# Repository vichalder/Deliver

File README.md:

# Deliver phase
This is where all the files created for the project are stored.

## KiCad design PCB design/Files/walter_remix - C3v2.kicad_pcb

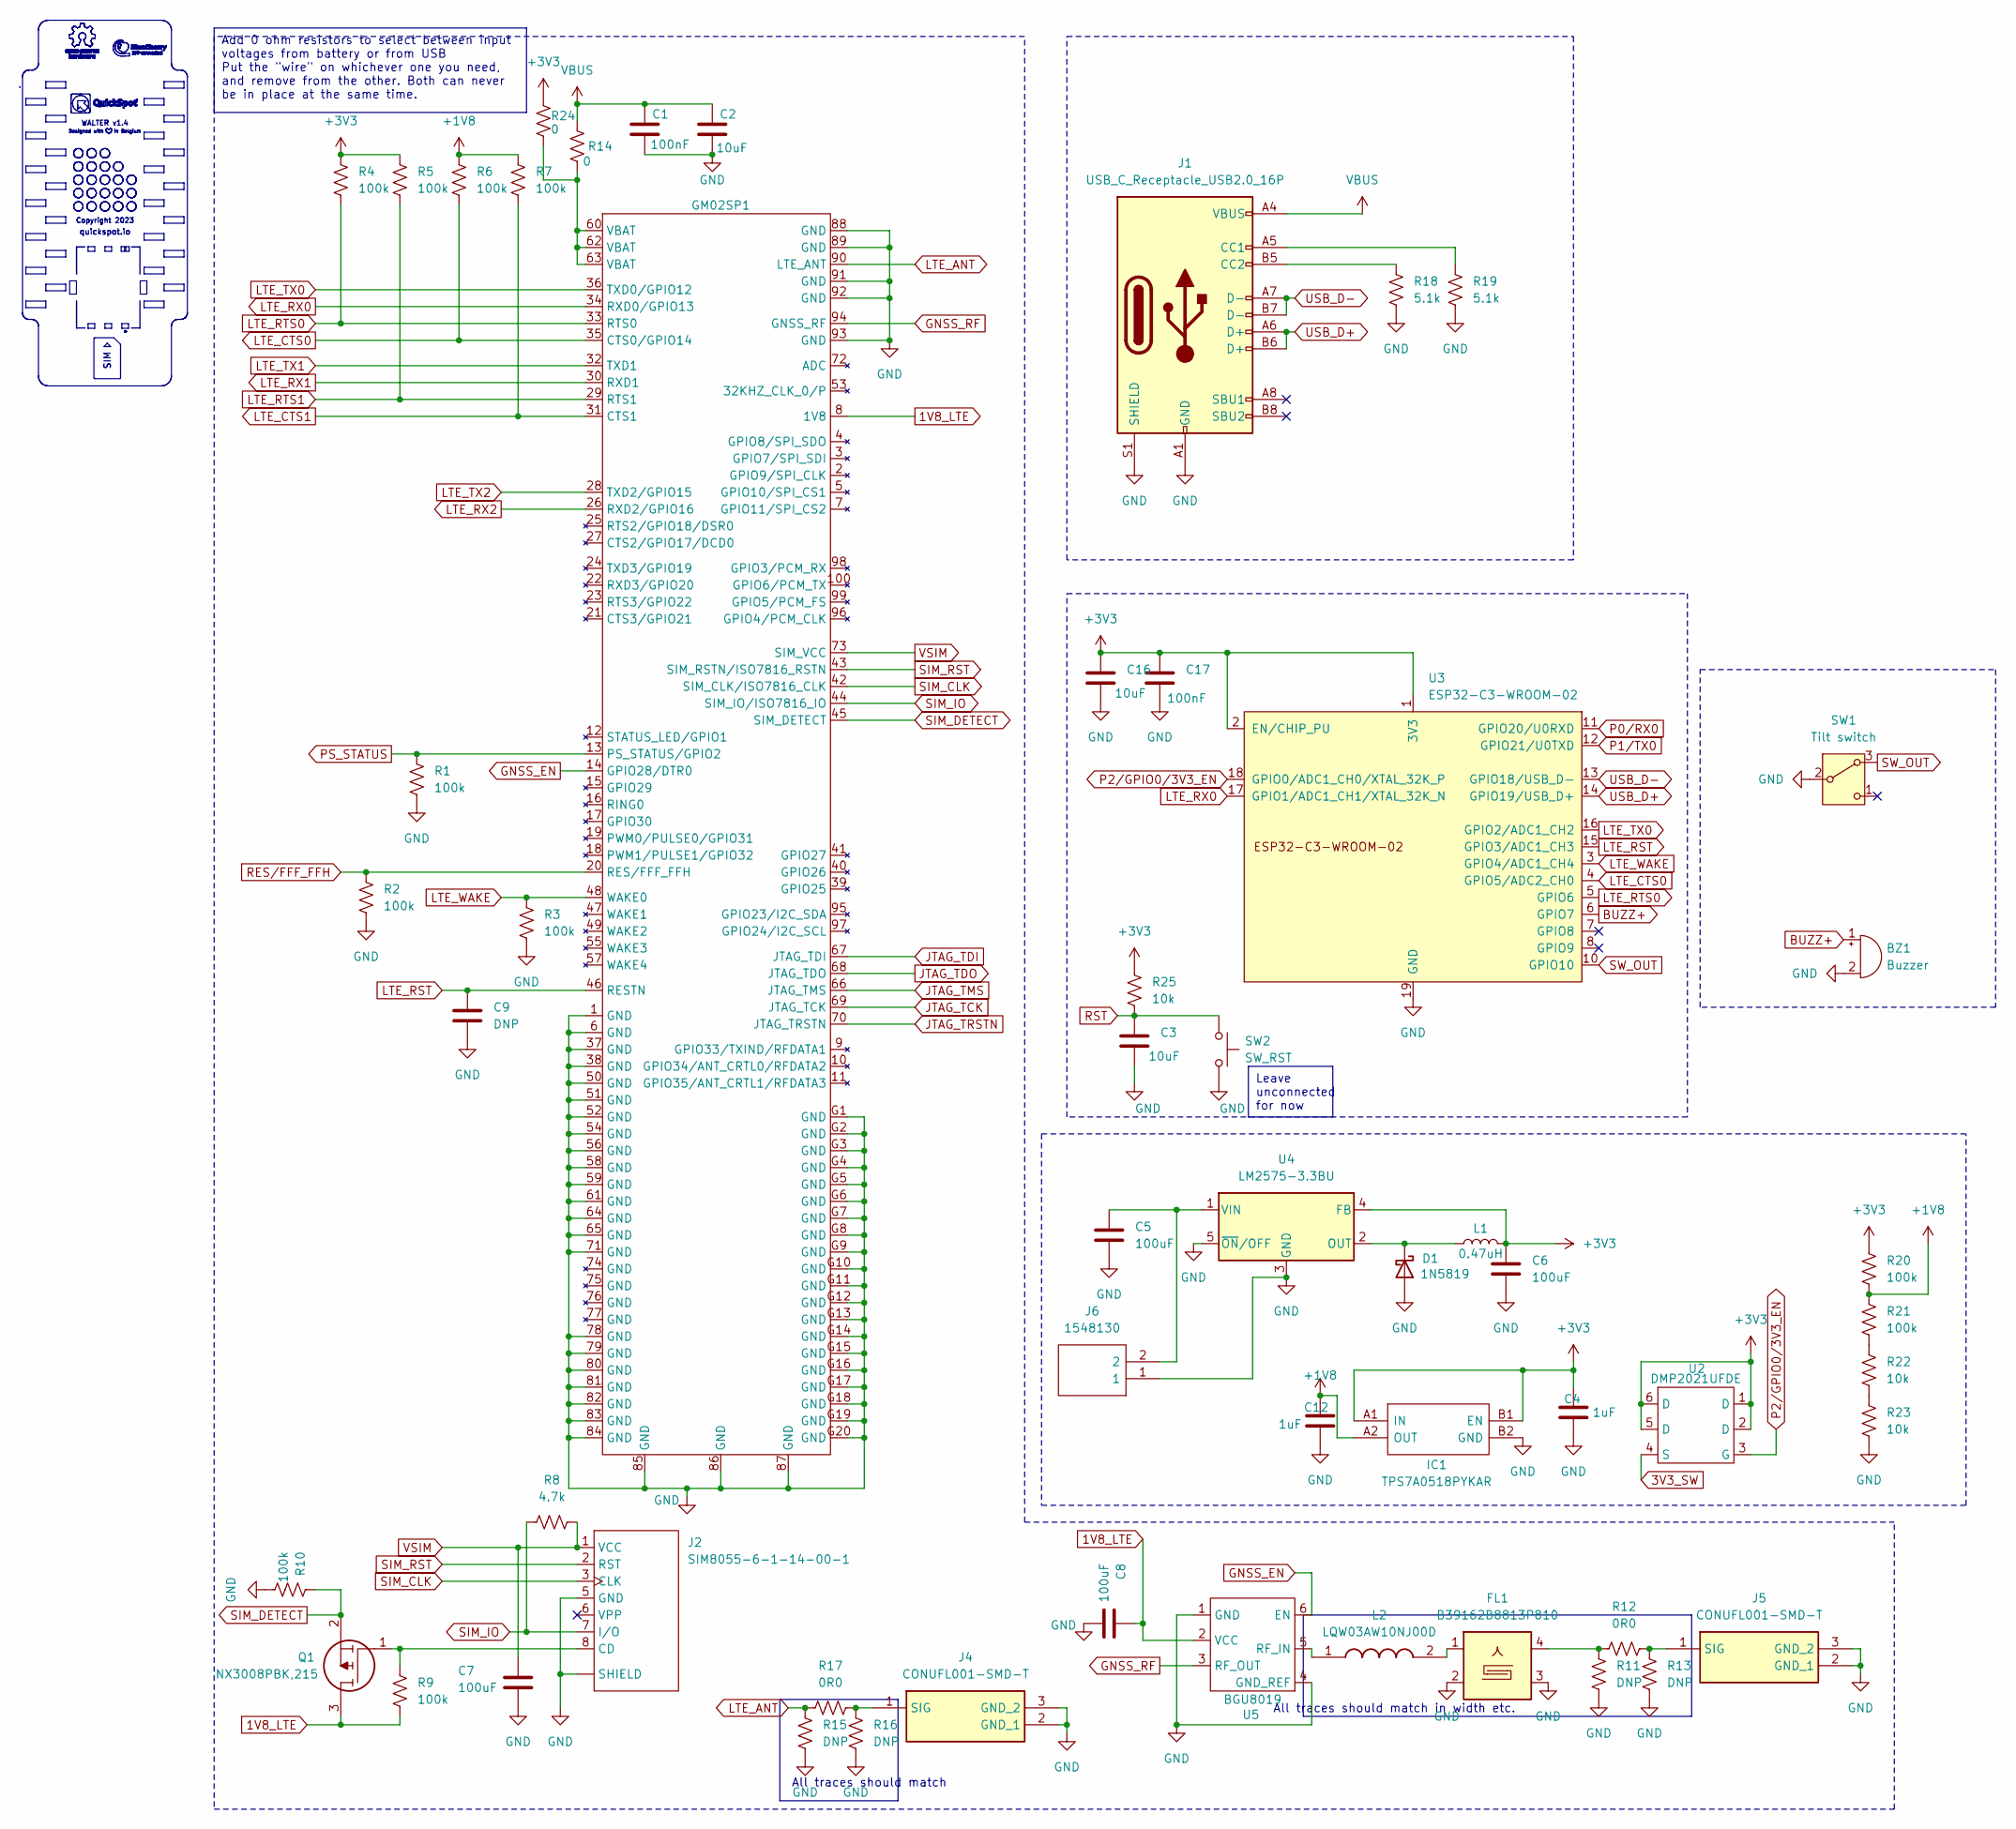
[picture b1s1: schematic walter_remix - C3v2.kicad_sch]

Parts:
BZ1: Buzzer; Buzzer_CUI_CPT-9019S-SMT
C1, C17: 100nF; C_0201_0603Metric
C2, C3, C16: 10uF; C_0201_0603Metric
C4, C12: 1uF; C_0201_0603Metric
C5, C6, C7, C8: 100uF; C_0201_0603Metric
C9: DNP; C_0201_0603Metric
D1: 1N5819; SOD3715X145N
FL1: B39162B8813P810; Filter_1109-5_1.1x0.9mm
GM02SP1: Sequans Monarch 2 GM02SP
IC1: TPS7A0518PYKAR; BGA4C35P2X2_66X66X40; Mouser Part Number 595-TPS7A0518PYKAR
J1: USB_C_Receptacle_USB2.0_16P; USB_C_Receptacle_HCTL_HC-TYPE-C-16P-01A
J2: SIM8055-6-1-14-00-1; SIM8055-6-1-14-01-A
J4, J5: CONUFL001-SMD-T; Mouser Part Number N/A
J6: 1548130; Mouser Part Number 651-1548130
L1: 0.47uH; Inductor 0.47uH
L2: LQW03AW10NJ00D; Mouser Part Number 81-LQW03AW10NJ00D
Q1: NX3008PBK,215; NX3008PBK215; Mouser Part Number 771-NX3008PBK,215
R1, R2, R3, R4, R5, R6, R7, R9, R10, R20, R21: 100k; R_0201_0603Metric
R8: 4.7k; R_0201_0603Metric
R11, R13, R15, R16: DNP; R_0201_0603Metric
R12, R17: 0R0; R_0201_0603Metric
R14, R24: 0; R_0201_0603Metric
R18, R19: 5.1k; R_0201_0603Metric
R22, R23, R25: 10k; R_0201_0603Metric
SW1: Tilt switch; Adafruit_vibration_sensor_tall
SW2: SW_RST; PTS815SJK250SMTRLFS
U2: DMP2021UFDE
U3: ESP32-C3-WROOM-02
U4: LM2575-3.3BU; TO-263-5_TabPin3
U5: BGU8019

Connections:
1V8_LTE: C8.1, GM02SP1.8 (1V8), Q1.3, R9.1, U5.2 (VCC)
+1V8: C12.1, IC1.A2 (OUT), R6.1, R7.1, R20.2, R21.1
+3V3: C4.1, C6.1, C16.1, C17.1, IC1.A1 (IN), IC1.B1 (EN), L1.2, R4.1, R5.1, R20.1, R24.1, R25.1, U2.1 (D), U2.2 (D), U2.5 (D), U2.6 (D), U3.1 (3V3), U3.2 (EN/CHIP_PU), U4.4 (FB)
BUZZ+: BZ1.1 (+), U3.6 (GPIO7)
GND: BZ1.2 (-), C1.2, C2.2, C3.2, C4.2, C5.2, C6.2, C7.2, C8.2, C9.2, C12.2, C16.2, C17.2, D1.2 (A), D1.A, FL1.2, FL1.3, FL1.5, GM02SP1.1 (GND), GM02SP1.6 (GND), GM02SP1.37 (GND), GM02SP1.38 (GND), GM02SP1.50 (GND), GM02SP1.51 (GND), GM02SP1.52 (GND), GM02SP1.54 (GND), GM02SP1.56 (GND), GM02SP1.58 (GND), GM02SP1.59 (GND), GM02SP1.61 (GND), GM02SP1.64 (GND), GM02SP1.65 (GND), GM02SP1.71 (GND), GM02SP1.78 (GND), GM02SP1.79 (GND), GM02SP1.80 (GND), GM02SP1.81 (GND), GM02SP1.82 (GND), GM02SP1.83 (GND), GM02SP1.84 (GND), GM02SP1.85 (GND), GM02SP1.86 (GND), GM02SP1.87 (GND), GM02SP1.88 (GND), GM02SP1.89 (GND), GM02SP1.91 (GND), GM02SP1.92 (GND), GM02SP1.93 (GND), GM02SP1.G1 (GND), GM02SP1.G2 (GND), GM02SP1.G3 (GND), GM02SP1.G4 (GND), GM02SP1.G5 (GND), GM02SP1.G6 (GND), GM02SP1.G7 (GND), GM02SP1.G8 (GND), GM02SP1.G9 (GND), GM02SP1.G10 (GND), GM02SP1.G11 (GND), GM02SP1.G12 (GND), GM02SP1.G13 (GND), GM02SP1.G14 (GND), GM02SP1.G15 (GND), GM02SP1.G16 (GND), GM02SP1.G17 (GND), GM02SP1.G18 (GND), GM02SP1.G19 (GND), GM02SP1.G20 (GND), IC1.B2 (GND), J1.A1 (GND), J1.A12 (GND), J1.B1 (GND), J1.B12 (GND), J1.S1 (SHIELD), J2. (SHIELD), J2.5 (GND), J4.2 (GND_1), J4.3 (GND_2), J5.2 (GND_1), J5.3 (GND_2), J6.1, R1.2, R2.2, R3.2, R10.1, R11.1, R13.1, R15.1, R16.1, R18.2, R19.2, R23.2, SW1.2 (B), SW2.3 (B), SW2.4 (B), U3.9 (GND), U3.19 (GND), U4.3 (GND), U4.5 (~ON/OFF), U5.1 (GND), U5.4 (GND_REF)
GNSS_EN: GM02SP1.14 (GPIO28/DTR0), U5.6 (EN)
GNSS_RF: GM02SP1.94 (GNSS_RF), U5.3 (RF_OUT)
JTAG_TCK: GM02SP1.69 (JTAG_TCK)
JTAG_TDI: GM02SP1.67 (JTAG_TDI)
JTAG_TDO: GM02SP1.68 (JTAG_TDO)
JTAG_TMS: GM02SP1.66 (JTAG_TMS)
JTAG_TRSTN: GM02SP1.70 (JTAG_TRSTN)
LTE_ANT: GM02SP1.90 (LTE_ANT), R15.2, R17.2
LTE_CTS0: GM02SP1.35 (CTS0/GPIO14), R6.2, U3.4 (GPIO5/ADC2_CH0)
LTE_CTS1: GM02SP1.31 (CTS1), R7.2
LTE_RST: C9.1, GM02SP1.46 (RESTN), U3.15 (GPIO3/ADC1_CH3)
LTE_RTS0: GM02SP1.33 (RTS0), R4.2, U3.5 (GPIO6)
LTE_RTS1: GM02SP1.29 (RTS1), R5.2
LTE_RX0: GM02SP1.34 (RXD0/GPIO13), U3.17 (GPIO1/ADC1_CH1/XTAL_32K_N)
LTE_RX1: GM02SP1.30 (RXD1)
LTE_RX2: GM02SP1.26 (RXD2/GPIO16)
LTE_TX0: GM02SP1.36 (TXD0/GPIO12), U3.16 (GPIO2/ADC1_CH2)
LTE_TX1: GM02SP1.32 (TXD1)
LTE_TX2: GM02SP1.28 (TXD2/GPIO15)
LTE_WAKE: GM02SP1.48 (WAKE0), R3.1, U3.3 (GPIO4/ADC1_CH4)
unnamed: D1.1 (K), D1.C, L1.1, U4.2 (OUT)
unnamed: FL1.1, L2.2
unnamed: FL1.4, R11.2, R12.2
unnamed: GM02SP1.60 (VBAT), GM02SP1.62 (VBAT), GM02SP1.63 (VBAT), R14.2, R24.2
unnamed: J1.A5 (CC1), R19.1
unnamed: J1.B5 (CC2), R18.1
unnamed: J2.8 (CD), Q1.1, R9.2
unnamed: J4.1 (SIG), R16.2, R17.1
unnamed: J5.1 (SIG), R12.1, R13.2
unnamed: R21.2, R22.1
unnamed: R22.2, R23.1
unnamed: C5.1, J6.2, U4.1 (VIN)
unnamed: L2.1, U5.5 (RF_IN)
P0/RX0: U3.11 (GPIO20/U0RXD)
P1/TX0: U3.12 (GPIO21/U0TXD)
P2/GPIO0/3V3_EN: U2.3 (G), U3.18 (GPIO0/ADC1_CH0/XTAL_32K_P)
PS_STATUS: GM02SP1.13 (PS_STATUS/GPIO2), R1.1
RES/FFF_FFH: GM02SP1.20 (RES/FFF_FFH), R2.1
RST: C3.1, R25.2, SW2.1 (A), SW2.2 (A)
SIM_CLK: GM02SP1.42 (SIM_CLK/ISO7816_CLK), J2.3 (CLK)
SIM_DETECT: GM02SP1.45 (SIM_DETECT), Q1.2, R10.2
SIM_IO: GM02SP1.44 (SIM_IO/ISO7816_IO), J2.7 (I/O), R8.1
SIM_RST: GM02SP1.43 (SIM_RSTN/ISO7816_RSTN), J2.2 (RST)
SW_OUT: SW1.3 (A), U3.10 (GPIO10)
USB_D+: J1.A6 (D+), J1.B6 (D+), U3.14 (GPIO19/USB_D+)
USB_D-: J1.A7 (D-), J1.B7 (D-), U3.13 (GPIO18/USB_D-)
VBUS: C1.1, C2.1, J1.A4 (VBUS), J1.A9 (VBUS), J1.B4 (VBUS), J1.B9 (VBUS), R14.1
VSIM: C7.1, GM02SP1.73 (SIM_VCC), J2.1 (VCC), R8.2

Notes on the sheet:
Leave unconnected for now
Add 0 ohm resistors to select between input voltages from battery or from USB Put the "wire" on whichever one you need, and remove from the other. Both can never be in place at the same time.
All traces should match
All traces should match in width etc.

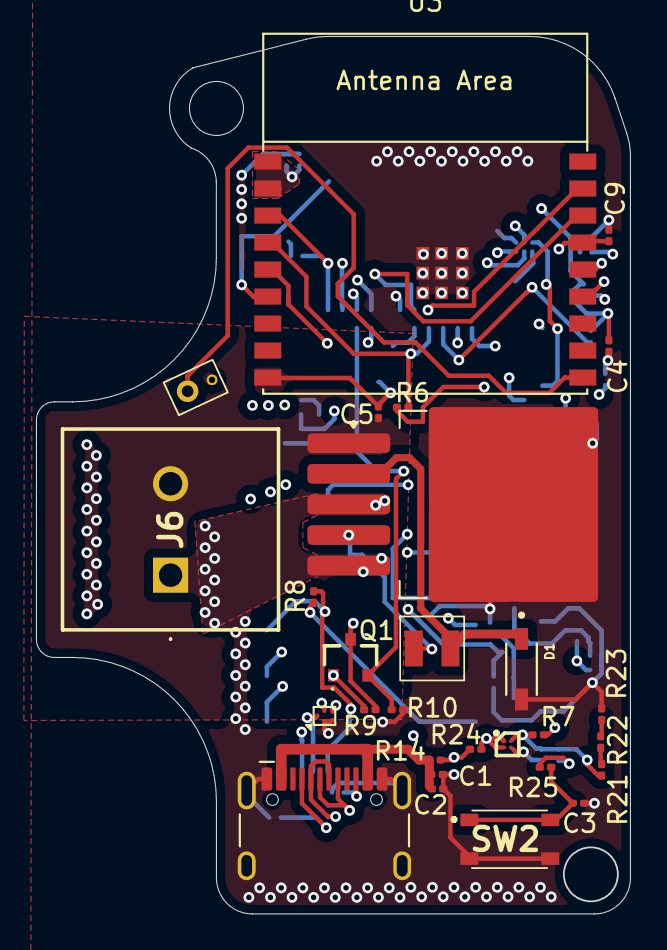
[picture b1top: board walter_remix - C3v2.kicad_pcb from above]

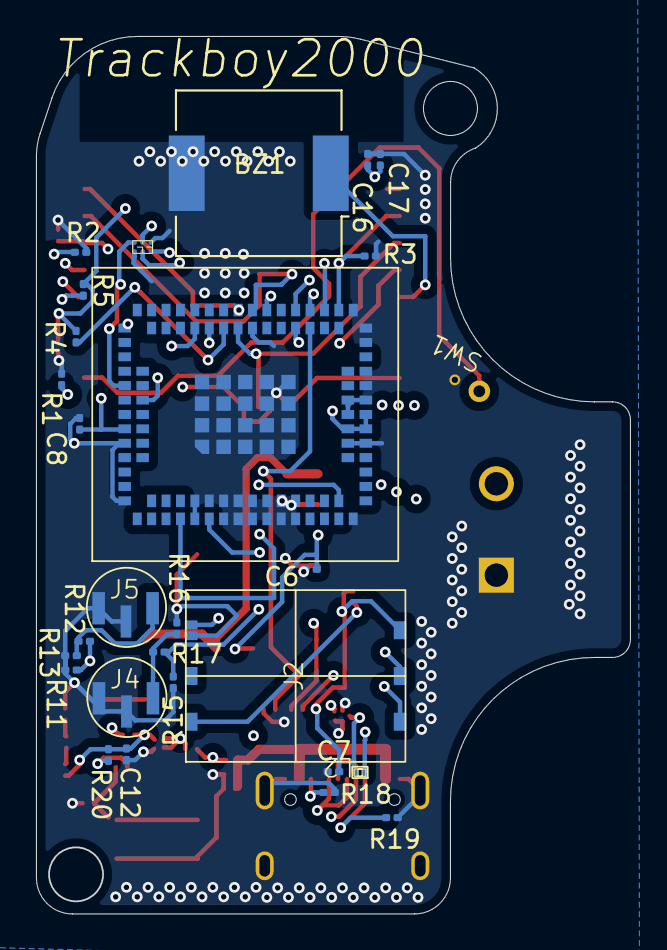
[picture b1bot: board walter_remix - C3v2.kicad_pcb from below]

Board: 4 copper layers, 33.0 x 48.8 mm, 55 parts (28 on the bottom side), 41 nets.

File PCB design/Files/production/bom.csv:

Designator,Footprint,Quantity,Value,LCSC Part #
BZ1,Buzzer_CUI_CPT-9019S-SMT,1,Buzzer,
"C1, C17",0201,2,100nF,
"C12, C4",0201,2,1uF,
"C16, C2, C3",0201,3,10uF,
"C5, C6, C7, C8",0201,4,100uF,
"C9, R11, R13, R15, R16",0201,5,DNP,
D1,SOD3715X145N,1,1N5819,
FL1,Filter_1109-5_1.1x0.9mm,1,B39162B8813P810,
GM02SP1,Sequans Monarch 2 GM02SP,1,~,
IC1,BGA4C35P2X2_66X66X40,1,TPS7A0518PYKAR,
J1,USB_C_Receptacle_HCTL_HC-TYPE-C-16P-01A,1,USB_C_Receptacle_USB2.0_16P,
J2,SIM8055-6-1-14-01-A,1,SIM8055-6-1-14-00-1,
"J4, J5",CONUFL001-SMD-T,2,CONUFL001-SMD-T,
J6,1548130,1,1548130,
L1,Inductor 0.47uH,1,0.47uH,
L2,LQW03AW10NJ00D,1,LQW03AW10NJ00D,
Q1,NX3008PBK215,1,"NX3008PBK,215",
"R1, R10, R2, R20, R21, R3, R4, R5, R6, R7, R9",0201,11,100k,
"R12, R17",0201,2,0R0,
"R14, R24",0201,2,0,
"R18, R19",0201,2,5.1k,
"R22, R23, R25",0201,3,10k,
R8,0201,1,4.7k,
SW1,Adafruit_vibration_sensor_tall,1,Tilt switch,
SW2,PTS815SJK250SMTRLFS,1,SW_RST,
U3,ESP32-C3-WROOM-02,1,ESP32-C3-WROOM-02,
U4,TO-263-5_TabPin3,1,LM2575-3.3BU,
U5,BGU8019,1,BGU8019,

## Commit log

2025-01-12 Update 12-01
2025-01-12 Added 1st iteration JLCPCB order
